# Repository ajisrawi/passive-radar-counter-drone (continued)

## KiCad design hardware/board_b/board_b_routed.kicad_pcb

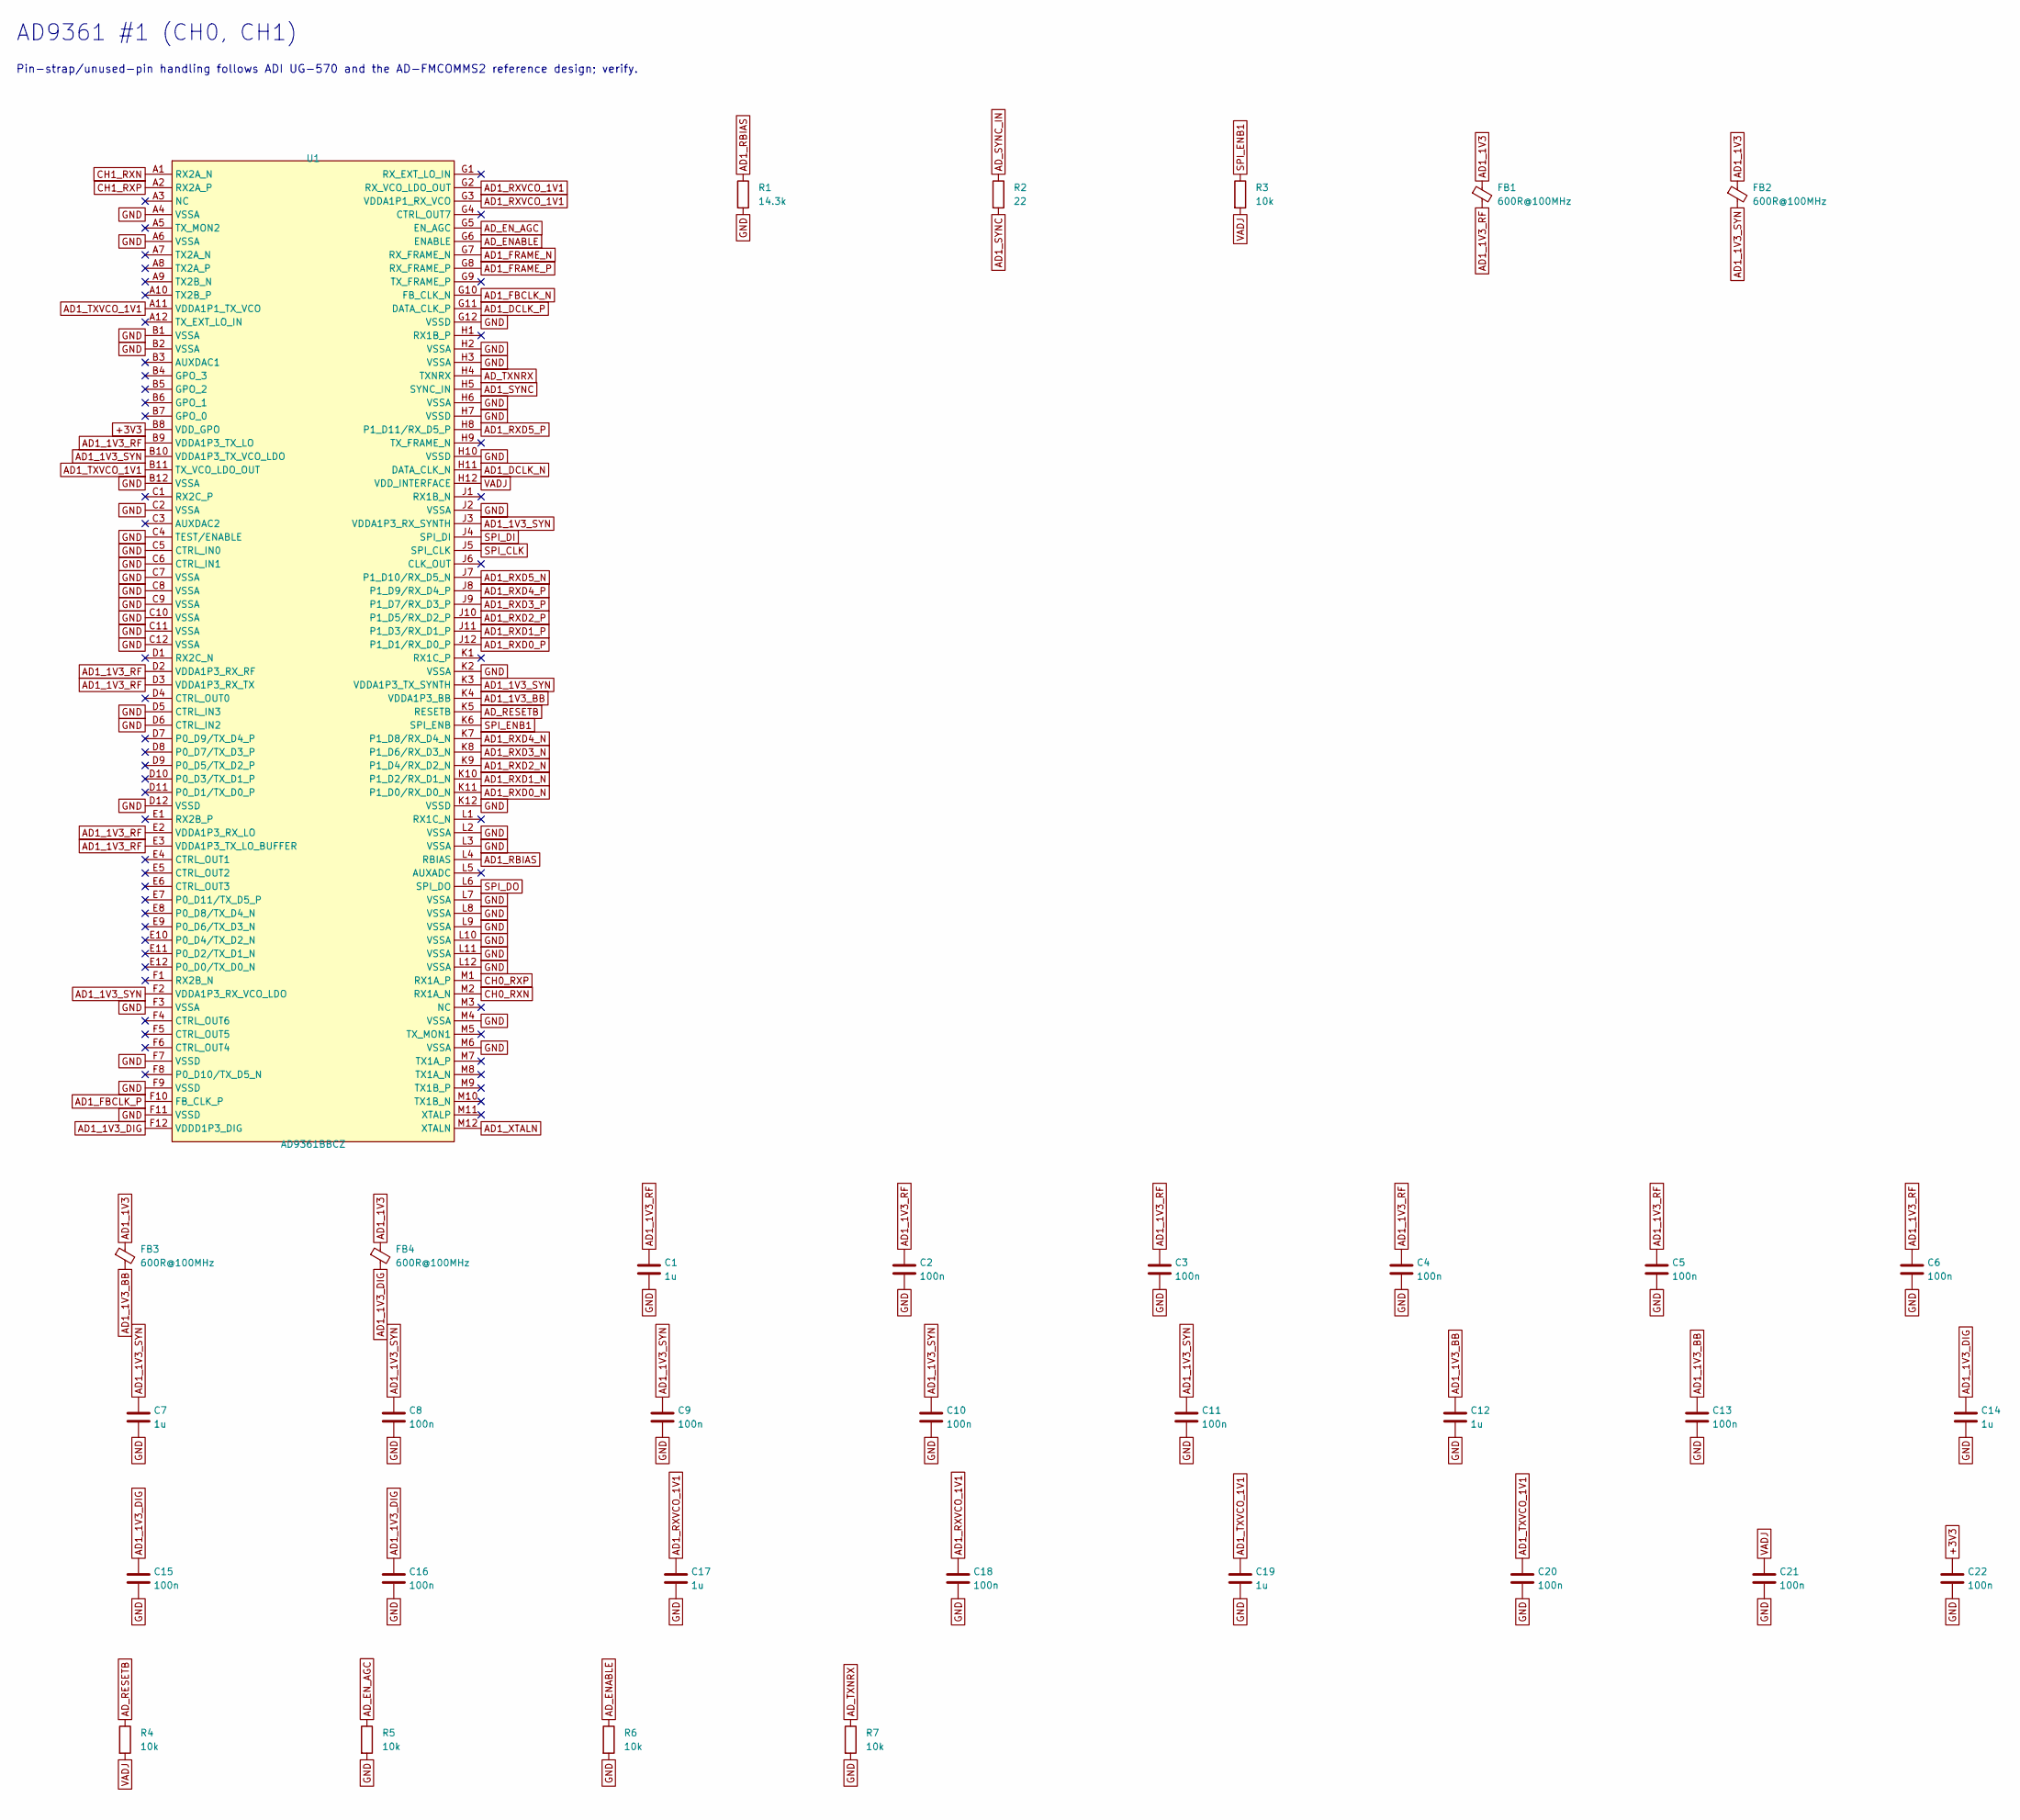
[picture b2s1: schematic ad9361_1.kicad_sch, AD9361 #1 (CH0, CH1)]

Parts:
C1, C7, C12, C14, C17, C19: 1u; C_0402_1005Metric; LCSC C52923
C2, C3, C4, C5, C6, C8, C9, C10, C11, C13, C15, C16, C18, C20, C21, C22: 100n; C_0402_1005Metric; LCSC C1525
FB1, FB2, FB3, FB4: 600R@100MHz; L_0603_1608Metric
R1: 14.3k; R_0402_1005Metric; Tolerance 1%
R2: 22; R_0402_1005Metric
R3, R4, R5, R6, R7: 10k; R_0402_1005Metric; LCSC C25744
U1: AD9361BBCZ; CSPBGA-144_L10.0-W10.0-R12-C12-P0.80-BL; MPN AD9361BBCZ; LCSC C515884

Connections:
+3V3: C22.1, U1.B8 (VDD_GPO); also elsewhere on the board
AD1_1V3: FB1.1, FB2.1, FB3.1, FB4.1; also elsewhere on the board
AD1_1V3_BB: C12.1, C13.1, FB3.2, U1.K4 (VDDA1P3_BB)
AD1_1V3_DIG: C14.1, C15.1, C16.1, FB4.2, U1.F12 (VDDD1P3_DIG)
AD1_1V3_RF: C1.1, C2.1, C3.1, C4.1, C5.1, C6.1, FB1.2, U1.B9 (VDDA1P3_TX_LO), U1.D2 (VDDA1P3_RX_RF), U1.D3 (VDDA1P3_RX_TX), U1.E2 (VDDA1P3_RX_LO), U1.E3 (VDDA1P3_TX_LO_BUFFER)
AD1_1V3_SYN: C7.1, C8.1, C9.1, C10.1, C11.1, FB2.2, U1.B10 (VDDA1P3_TX_VCO_LDO), U1.F2 (VDDA1P3_RX_VCO_LDO), U1.J3 (VDDA1P3_RX_SYNTH), U1.K3 (VDDA1P3_TX_SYNTH)
AD1_DCLK_N: U1.H11 (DATA_CLK_N); also elsewhere on the board
AD1_DCLK_P: U1.G11 (DATA_CLK_P); also elsewhere on the board
AD1_FBCLK_N: U1.G10 (FB_CLK_N); also elsewhere on the board
AD1_FBCLK_P: U1.F10 (FB_CLK_P); also elsewhere on the board
AD1_FRAME_N: U1.G7 (RX_FRAME_N); also elsewhere on the board
AD1_FRAME_P: U1.G8 (RX_FRAME_P); also elsewhere on the board
AD1_RBIAS: R1.1, U1.L4 (RBIAS)
AD1_RXD0_N: U1.K11 (P1_D0/RX_D0_N); also elsewhere on the board
AD1_RXD0_P: U1.J12 (P1_D1/RX_D0_P); also elsewhere on the board
AD1_RXD1_N: U1.K10 (P1_D2/RX_D1_N); also elsewhere on the board
AD1_RXD1_P: U1.J11 (P1_D3/RX_D1_P); also elsewhere on the board
AD1_RXD2_N: U1.K9 (P1_D4/RX_D2_N); also elsewhere on the board
AD1_RXD2_P: U1.J10 (P1_D5/RX_D2_P); also elsewhere on the board
AD1_RXD3_N: U1.K8 (P1_D6/RX_D3_N); also elsewhere on the board
AD1_RXD3_P: U1.J9 (P1_D7/RX_D3_P); also elsewhere on the board
AD1_RXD4_N: U1.K7 (P1_D8/RX_D4_N); also elsewhere on the board
AD1_RXD4_P: U1.J8 (P1_D9/RX_D4_P); also elsewhere on the board
AD1_RXD5_N: U1.J7 (P1_D10/RX_D5_N); also elsewhere on the board
AD1_RXD5_P: U1.H8 (P1_D11/RX_D5_P); also elsewhere on the board
AD1_RXVCO_1V1: C17.1, C18.1, U1.G2 (RX_VCO_LDO_OUT), U1.G3 (VDDA1P1_RX_VCO)
AD1_SYNC: R2.2, U1.H5 (SYNC_IN)
AD1_TXVCO_1V1: C19.1, C20.1, U1.A11 (VDDA1P1_TX_VCO), U1.B11 (TX_VCO_LDO_OUT)
AD1_XTALN: U1.M12 (XTALN); also elsewhere on the board
AD_ENABLE: R6.1, U1.G6 (ENABLE); also elsewhere on the board
AD_EN_AGC: R5.1, U1.G5 (EN_AGC); also elsewhere on the board
AD_RESETB: R4.1, U1.K5 (RESETB); also elsewhere on the board
AD_SYNC_IN: R2.1; also elsewhere on the board
AD_TXNRX: R7.1, U1.H4 (TXNRX); also elsewhere on the board
CH0_RXN: U1.M2 (RX1A_N); also elsewhere on the board
CH0_RXP: U1.M1 (RX1A_P); also elsewhere on the board
CH1_RXN: U1.A1 (RX2A_N); also elsewhere on the board
CH1_RXP: U1.A2 (RX2A_P); also elsewhere on the board
GND: C1.2, C2.2, C3.2, C4.2, C5.2, C6.2, C7.2, C8.2, C9.2, C10.2, C11.2, C12.2, C13.2, C14.2, C15.2, C16.2, C17.2, C18.2, C19.2, C20.2, C21.2, C22.2, R1.2, R5.2, R6.2, R7.2, U1.A4 (VSSA), U1.A6 (VSSA), U1.B1 (VSSA), U1.B2 (VSSA), U1.B12 (VSSA), U1.C2 (VSSA), U1.C4 (TEST/ENABLE), U1.C5 (CTRL_IN0), U1.C6 (CTRL_IN1), U1.C7 (VSSA), U1.C8 (VSSA), U1.C9 (VSSA), U1.C10 (VSSA), U1.C11 (VSSA), U1.C12 (VSSA), U1.D5 (CTRL_IN3), U1.D6 (CTRL_IN2), U1.D12 (VSSD), U1.F3 (VSSA), U1.F7 (VSSD), U1.F9 (VSSD), U1.F11 (VSSD), U1.G12 (VSSD), U1.H2 (VSSA), U1.H3 (VSSA), U1.H6 (VSSA), U1.H7 (VSSD), U1.H10 (VSSD), U1.J2 (VSSA), U1.K2 (VSSA), U1.K12 (VSSD), U1.L2 (VSSA), U1.L3 (VSSA), U1.L7 (VSSA), U1.L8 (VSSA), U1.L9 (VSSA), U1.L10 (VSSA), U1.L11 (VSSA), U1.L12 (VSSA), U1.M4 (VSSA), U1.M6 (VSSA); also elsewhere on the board
SPI_CLK: U1.J5 (SPI_CLK); also elsewhere on the board
SPI_DI: U1.J4 (SPI_DI); also elsewhere on the board
SPI_DO: U1.L6 (SPI_DO); also elsewhere on the board
SPI_ENB1: R3.1, U1.K6 (SPI_ENB); also elsewhere on the board
VADJ: C21.1, R3.2, R4.2, U1.H12 (VDD_INTERFACE); also elsewhere on the board

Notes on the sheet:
AD9361 #1 (CH0, CH1)
Pin-strap/unused-pin handling follows ADI UG-570 and the AD-FMCOMMS2 reference design; verify.

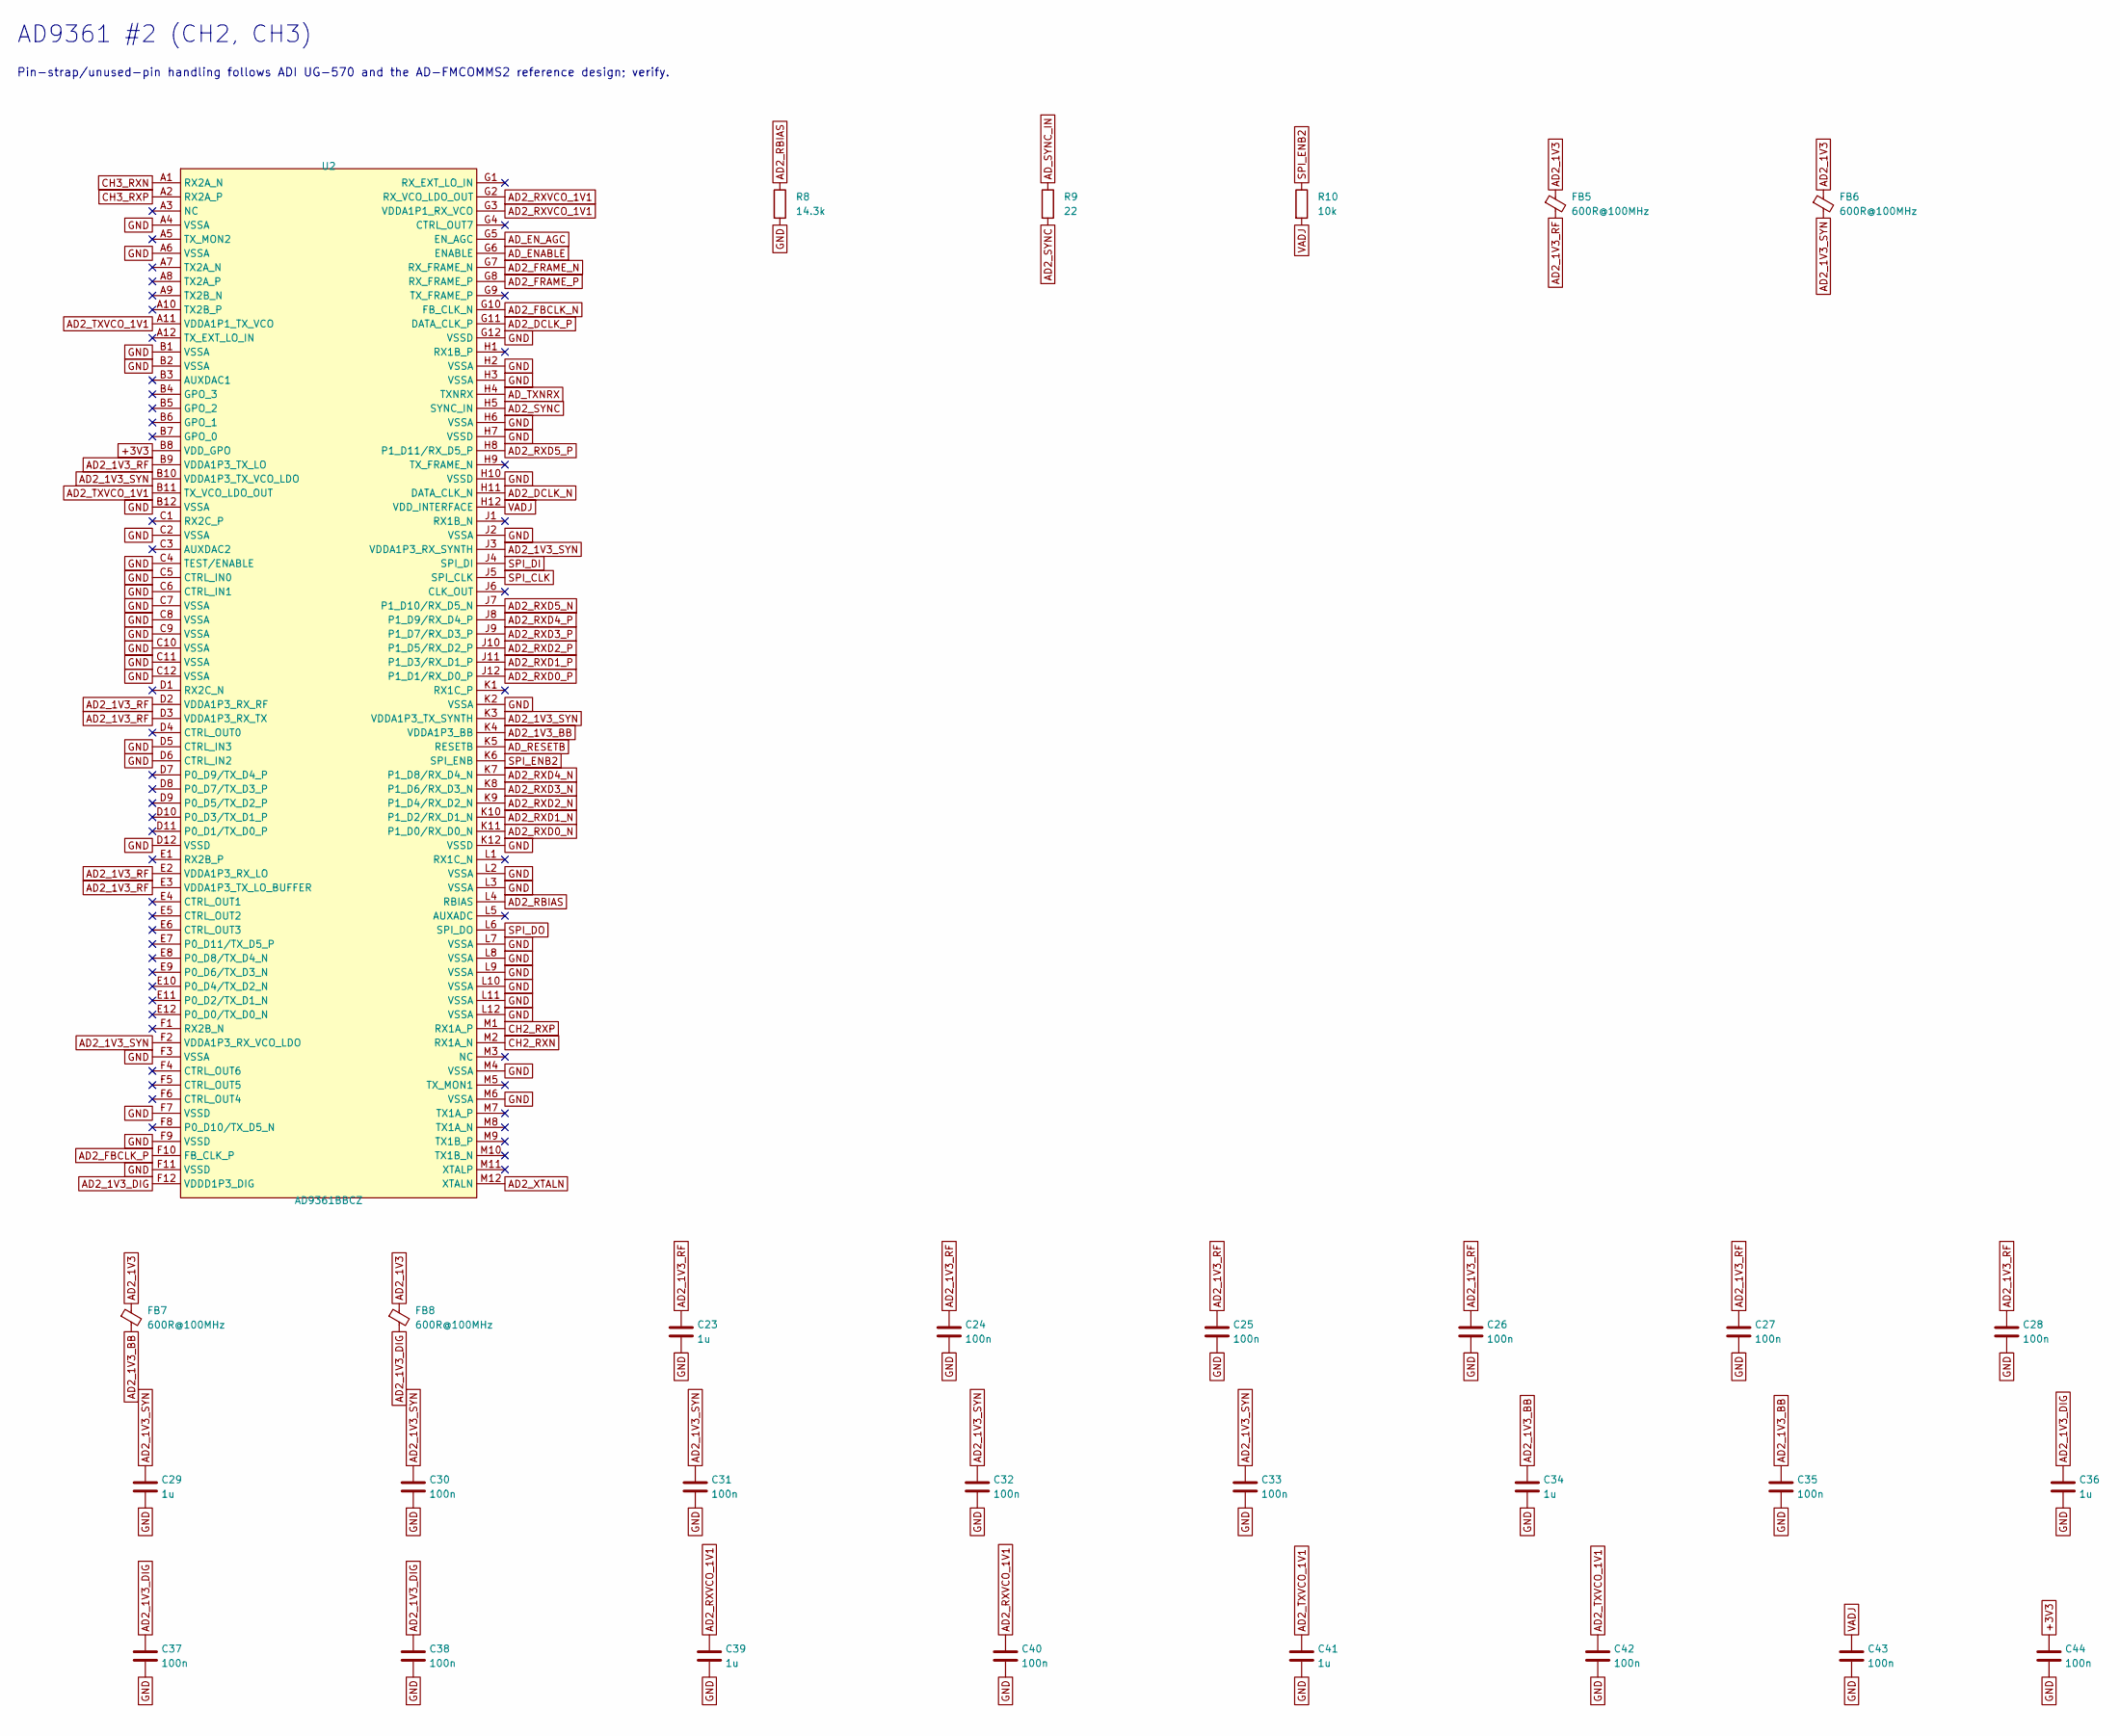
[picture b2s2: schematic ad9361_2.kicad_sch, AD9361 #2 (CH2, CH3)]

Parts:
C23, C29, C34, C36, C39, C41: 1u; C_0402_1005Metric; LCSC C52923
C24, C25, C26, C27, C28, C30, C31, C32, C33, C35, C37, C38, C40, C42, C43, C44: 100n; C_0402_1005Metric; LCSC C1525
FB5, FB6, FB7, FB8: 600R@100MHz; L_0603_1608Metric
R8: 14.3k; R_0402_1005Metric; Tolerance 1%
R9: 22; R_0402_1005Metric
R10: 10k; R_0402_1005Metric; LCSC C25744
U2: AD9361BBCZ; CSPBGA-144_L10.0-W10.0-R12-C12-P0.80-BL; MPN AD9361BBCZ; LCSC C515884

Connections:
+3V3: C44.1, U2.B8 (VDD_GPO); also elsewhere on the board
AD2_1V3: FB5.1, FB6.1, FB7.1, FB8.1; also elsewhere on the board
AD2_1V3_BB: C34.1, C35.1, FB7.2, U2.K4 (VDDA1P3_BB)
AD2_1V3_DIG: C36.1, C37.1, C38.1, FB8.2, U2.F12 (VDDD1P3_DIG)
AD2_1V3_RF: C23.1, C24.1, C25.1, C26.1, C27.1, C28.1, FB5.2, U2.B9 (VDDA1P3_TX_LO), U2.D2 (VDDA1P3_RX_RF), U2.D3 (VDDA1P3_RX_TX), U2.E2 (VDDA1P3_RX_LO), U2.E3 (VDDA1P3_TX_LO_BUFFER)
AD2_1V3_SYN: C29.1, C30.1, C31.1, C32.1, C33.1, FB6.2, U2.B10 (VDDA1P3_TX_VCO_LDO), U2.F2 (VDDA1P3_RX_VCO_LDO), U2.J3 (VDDA1P3_RX_SYNTH), U2.K3 (VDDA1P3_TX_SYNTH)
AD2_DCLK_N: U2.H11 (DATA_CLK_N); also elsewhere on the board
AD2_DCLK_P: U2.G11 (DATA_CLK_P); also elsewhere on the board
AD2_FBCLK_N: U2.G10 (FB_CLK_N); also elsewhere on the board
AD2_FBCLK_P: U2.F10 (FB_CLK_P); also elsewhere on the board
AD2_FRAME_N: U2.G7 (RX_FRAME_N); also elsewhere on the board
AD2_FRAME_P: U2.G8 (RX_FRAME_P); also elsewhere on the board
AD2_RBIAS: R8.1, U2.L4 (RBIAS)
AD2_RXD0_N: U2.K11 (P1_D0/RX_D0_N); also elsewhere on the board
AD2_RXD0_P: U2.J12 (P1_D1/RX_D0_P); also elsewhere on the board
AD2_RXD1_N: U2.K10 (P1_D2/RX_D1_N); also elsewhere on the board
AD2_RXD1_P: U2.J11 (P1_D3/RX_D1_P); also elsewhere on the board
AD2_RXD2_N: U2.K9 (P1_D4/RX_D2_N); also elsewhere on the board
AD2_RXD2_P: U2.J10 (P1_D5/RX_D2_P); also elsewhere on the board
AD2_RXD3_N: U2.K8 (P1_D6/RX_D3_N); also elsewhere on the board
AD2_RXD3_P: U2.J9 (P1_D7/RX_D3_P); also elsewhere on the board
AD2_RXD4_N: U2.K7 (P1_D8/RX_D4_N); also elsewhere on the board
AD2_RXD4_P: U2.J8 (P1_D9/RX_D4_P); also elsewhere on the board
AD2_RXD5_N: U2.J7 (P1_D10/RX_D5_N); also elsewhere on the board
AD2_RXD5_P: U2.H8 (P1_D11/RX_D5_P); also elsewhere on the board
AD2_RXVCO_1V1: C39.1, C40.1, U2.G2 (RX_VCO_LDO_OUT), U2.G3 (VDDA1P1_RX_VCO)
AD2_SYNC: R9.2, U2.H5 (SYNC_IN)
AD2_TXVCO_1V1: C41.1, C42.1, U2.A11 (VDDA1P1_TX_VCO), U2.B11 (TX_VCO_LDO_OUT)
AD2_XTALN: U2.M12 (XTALN); also elsewhere on the board
AD_ENABLE: U2.G6 (ENABLE); also elsewhere on the board
AD_EN_AGC: U2.G5 (EN_AGC); also elsewhere on the board
AD_RESETB: U2.K5 (RESETB); also elsewhere on the board
AD_SYNC_IN: R9.1; also elsewhere on the board
AD_TXNRX: U2.H4 (TXNRX); also elsewhere on the board
CH2_RXN: U2.M2 (RX1A_N); also elsewhere on the board
CH2_RXP: U2.M1 (RX1A_P); also elsewhere on the board
CH3_RXN: U2.A1 (RX2A_N); also elsewhere on the board
CH3_RXP: U2.A2 (RX2A_P); also elsewhere on the board
GND: C23.2, C24.2, C25.2, C26.2, C27.2, C28.2, C29.2, C30.2, C31.2, C32.2, C33.2, C34.2, C35.2, C36.2, C37.2, C38.2, C39.2, C40.2, C41.2, C42.2, C43.2, C44.2, R8.2, U2.A4 (VSSA), U2.A6 (VSSA), U2.B1 (VSSA), U2.B2 (VSSA), U2.B12 (VSSA), U2.C2 (VSSA), U2.C4 (TEST/ENABLE), U2.C5 (CTRL_IN0), U2.C6 (CTRL_IN1), U2.C7 (VSSA), U2.C8 (VSSA), U2.C9 (VSSA), U2.C10 (VSSA), U2.C11 (VSSA), U2.C12 (VSSA), U2.D5 (CTRL_IN3), U2.D6 (CTRL_IN2), U2.D12 (VSSD), U2.F3 (VSSA), U2.F7 (VSSD), U2.F9 (VSSD), U2.F11 (VSSD), U2.G12 (VSSD), U2.H2 (VSSA), U2.H3 (VSSA), U2.H6 (VSSA), U2.H7 (VSSD), U2.H10 (VSSD), U2.J2 (VSSA), U2.K2 (VSSA), U2.K12 (VSSD), U2.L2 (VSSA), U2.L3 (VSSA), U2.L7 (VSSA), U2.L8 (VSSA), U2.L9 (VSSA), U2.L10 (VSSA), U2.L11 (VSSA), U2.L12 (VSSA), U2.M4 (VSSA), U2.M6 (VSSA); also elsewhere on the board
SPI_CLK: U2.J5 (SPI_CLK); also elsewhere on the board
SPI_DI: U2.J4 (SPI_DI); also elsewhere on the board
SPI_DO: U2.L6 (SPI_DO); also elsewhere on the board
SPI_ENB2: R10.1, U2.K6 (SPI_ENB); also elsewhere on the board
VADJ: C43.1, R10.2, U2.H12 (VDD_INTERFACE); also elsewhere on the board

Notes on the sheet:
AD9361 #2 (CH2, CH3)
Pin-strap/unused-pin handling follows ADI UG-570 and the AD-FMCOMMS2 reference design; verify.

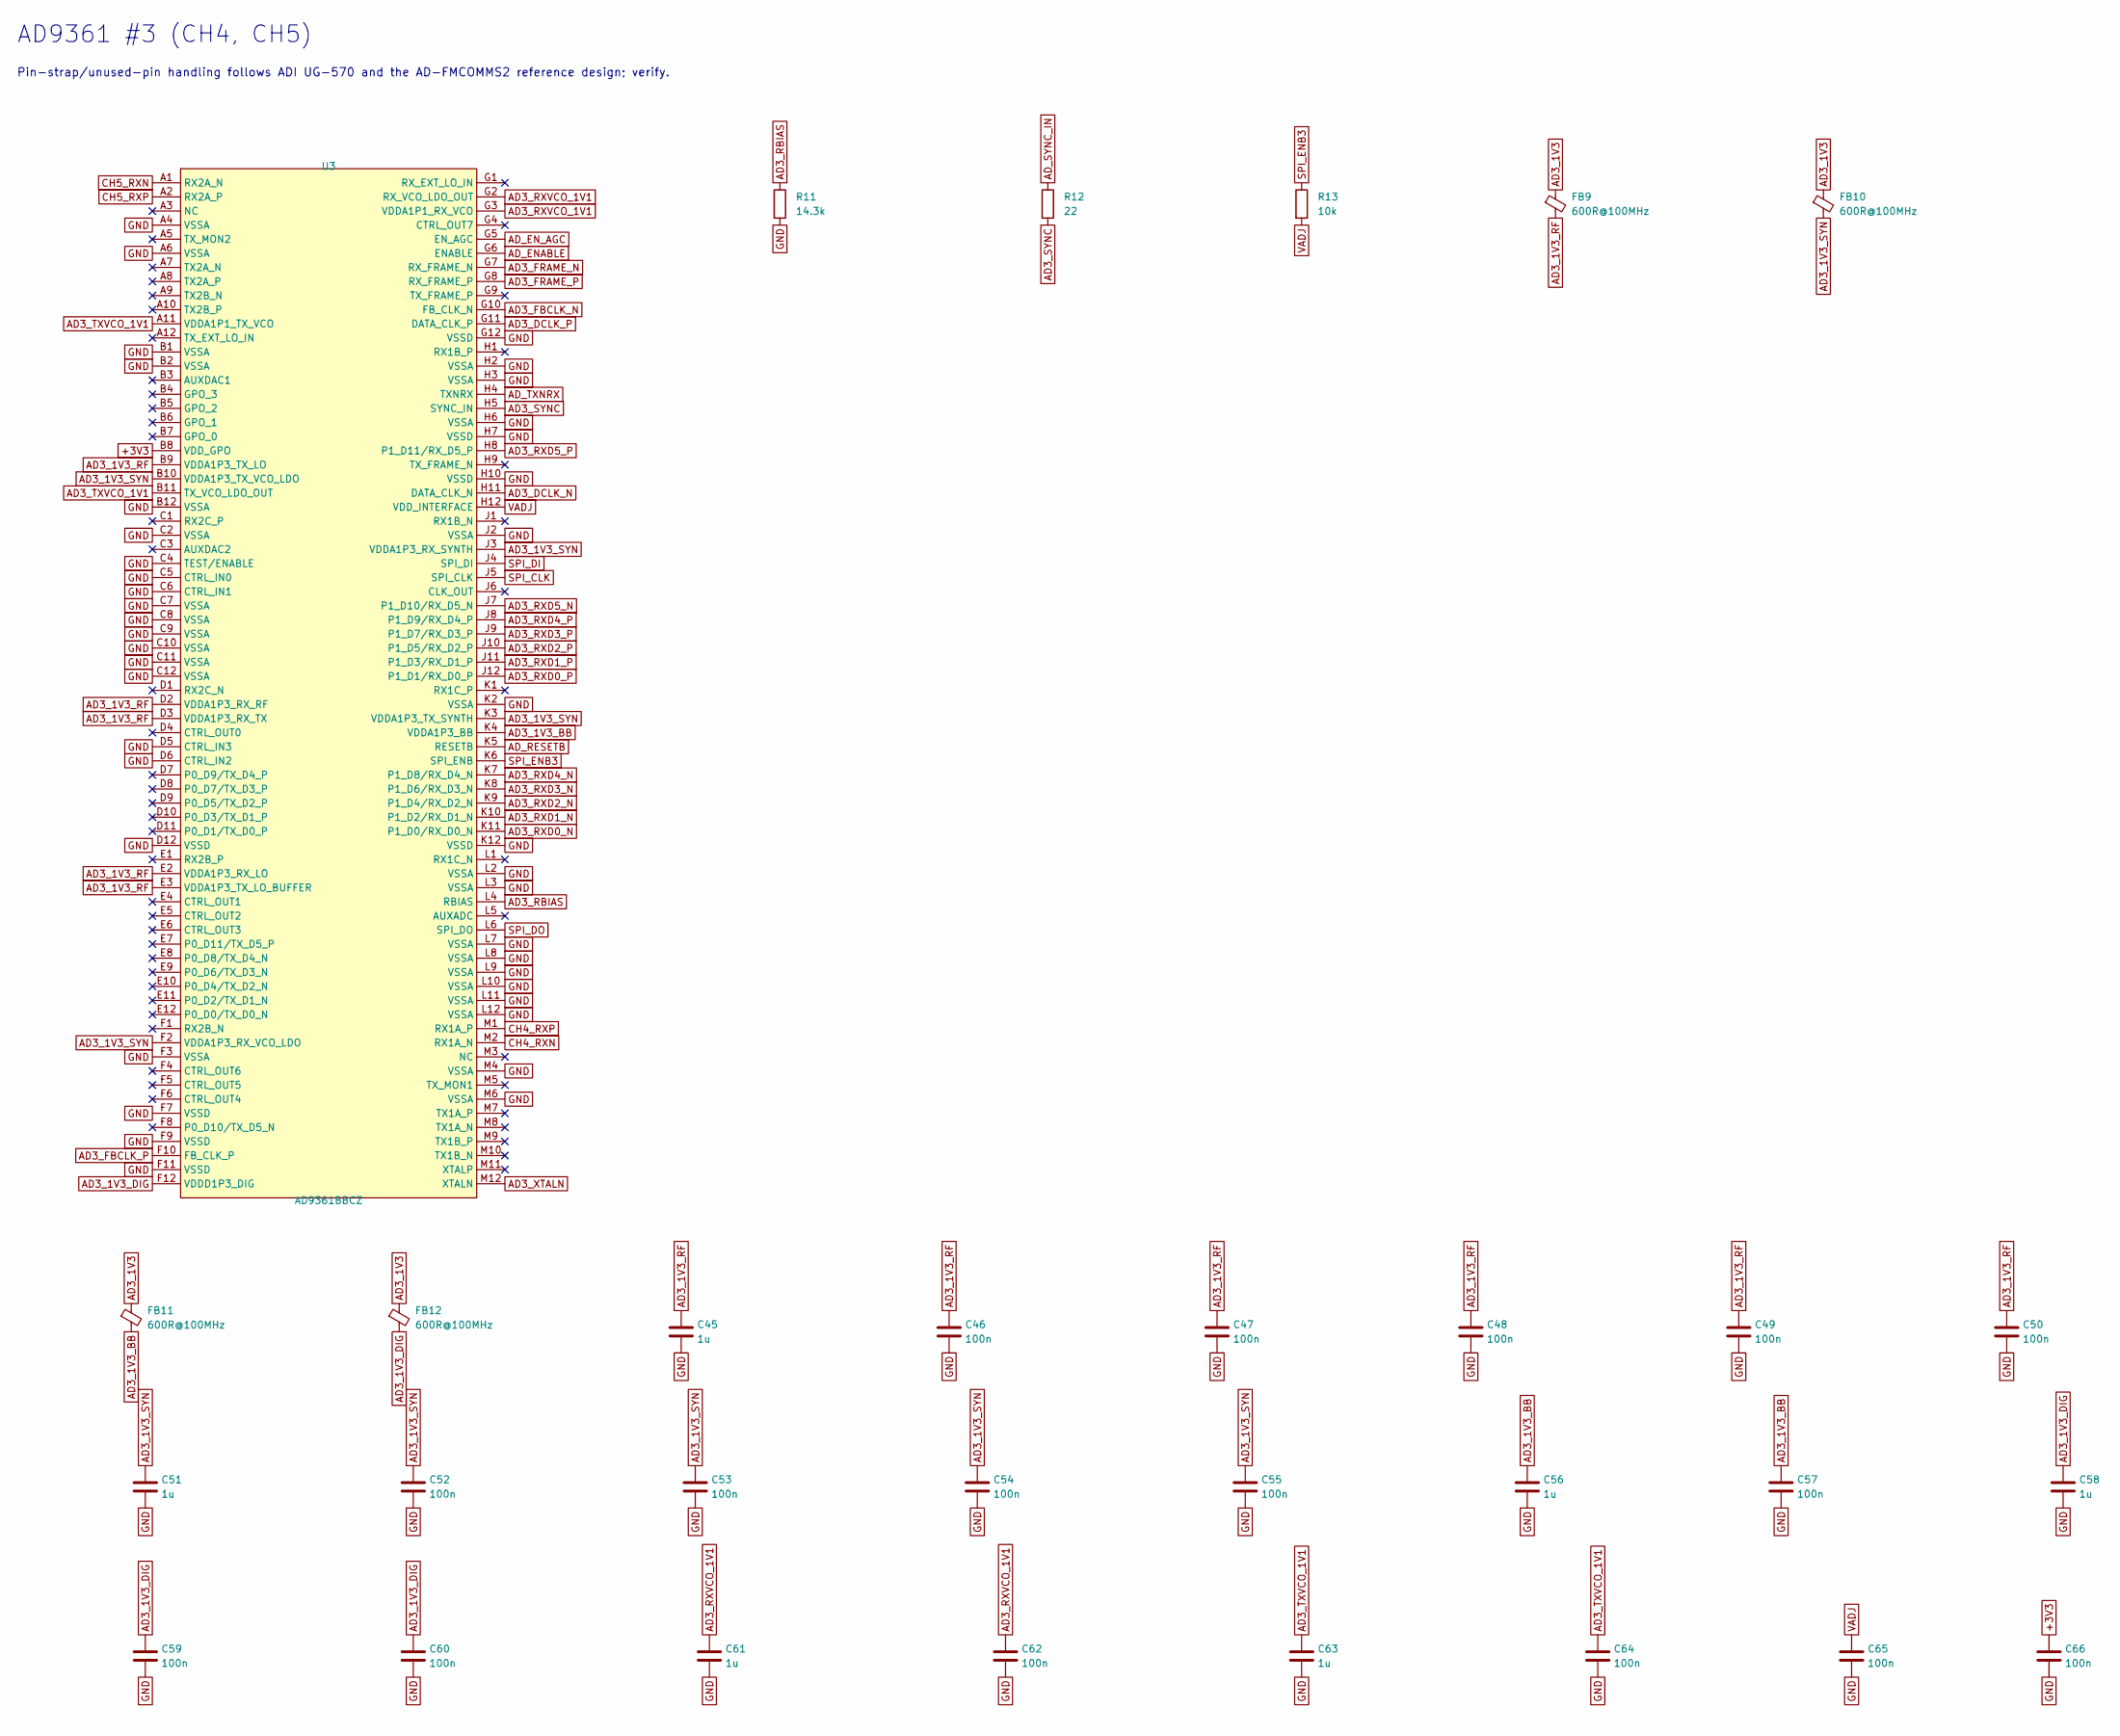
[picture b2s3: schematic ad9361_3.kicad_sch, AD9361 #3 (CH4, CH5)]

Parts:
C45, C51, C56, C58, C61, C63: 1u; C_0402_1005Metric; LCSC C52923
C46, C47, C48, C49, C50, C52, C53, C54, C55, C57, C59, C60, C62, C64, C65, C66: 100n; C_0402_1005Metric; LCSC C1525
FB9, FB10, FB11, FB12: 600R@100MHz; L_0603_1608Metric
R11: 14.3k; R_0402_1005Metric; Tolerance 1%
R12: 22; R_0402_1005Metric
R13: 10k; R_0402_1005Metric; LCSC C25744
U3: AD9361BBCZ; CSPBGA-144_L10.0-W10.0-R12-C12-P0.80-BL; MPN AD9361BBCZ; LCSC C515884

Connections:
+3V3: C66.1, U3.B8 (VDD_GPO); also elsewhere on the board
AD3_1V3: FB9.1, FB10.1, FB11.1, FB12.1; also elsewhere on the board
AD3_1V3_BB: C56.1, C57.1, FB11.2, U3.K4 (VDDA1P3_BB)
AD3_1V3_DIG: C58.1, C59.1, C60.1, FB12.2, U3.F12 (VDDD1P3_DIG)
AD3_1V3_RF: C45.1, C46.1, C47.1, C48.1, C49.1, C50.1, FB9.2, U3.B9 (VDDA1P3_TX_LO), U3.D2 (VDDA1P3_RX_RF), U3.D3 (VDDA1P3_RX_TX), U3.E2 (VDDA1P3_RX_LO), U3.E3 (VDDA1P3_TX_LO_BUFFER)
AD3_1V3_SYN: C51.1, C52.1, C53.1, C54.1, C55.1, FB10.2, U3.B10 (VDDA1P3_TX_VCO_LDO), U3.F2 (VDDA1P3_RX_VCO_LDO), U3.J3 (VDDA1P3_RX_SYNTH), U3.K3 (VDDA1P3_TX_SYNTH)
AD3_DCLK_N: U3.H11 (DATA_CLK_N); also elsewhere on the board
AD3_DCLK_P: U3.G11 (DATA_CLK_P); also elsewhere on the board
AD3_FBCLK_N: U3.G10 (FB_CLK_N); also elsewhere on the board
AD3_FBCLK_P: U3.F10 (FB_CLK_P); also elsewhere on the board
AD3_FRAME_N: U3.G7 (RX_FRAME_N); also elsewhere on the board
AD3_FRAME_P: U3.G8 (RX_FRAME_P); also elsewhere on the board
AD3_RBIAS: R11.1, U3.L4 (RBIAS)
AD3_RXD0_N: U3.K11 (P1_D0/RX_D0_N); also elsewhere on the board
AD3_RXD0_P: U3.J12 (P1_D1/RX_D0_P); also elsewhere on the board
AD3_RXD1_N: U3.K10 (P1_D2/RX_D1_N); also elsewhere on the board
AD3_RXD1_P: U3.J11 (P1_D3/RX_D1_P); also elsewhere on the board
AD3_RXD2_N: U3.K9 (P1_D4/RX_D2_N); also elsewhere on the board
AD3_RXD2_P: U3.J10 (P1_D5/RX_D2_P); also elsewhere on the board
AD3_RXD3_N: U3.K8 (P1_D6/RX_D3_N); also elsewhere on the board
AD3_RXD3_P: U3.J9 (P1_D7/RX_D3_P); also elsewhere on the board
AD3_RXD4_N: U3.K7 (P1_D8/RX_D4_N); also elsewhere on the board
AD3_RXD4_P: U3.J8 (P1_D9/RX_D4_P); also elsewhere on the board
AD3_RXD5_N: U3.J7 (P1_D10/RX_D5_N); also elsewhere on the board
AD3_RXD5_P: U3.H8 (P1_D11/RX_D5_P); also elsewhere on the board
AD3_RXVCO_1V1: C61.1, C62.1, U3.G2 (RX_VCO_LDO_OUT), U3.G3 (VDDA1P1_RX_VCO)
AD3_SYNC: R12.2, U3.H5 (SYNC_IN)
AD3_TXVCO_1V1: C63.1, C64.1, U3.A11 (VDDA1P1_TX_VCO), U3.B11 (TX_VCO_LDO_OUT)
AD3_XTALN: U3.M12 (XTALN); also elsewhere on the board
AD_ENABLE: U3.G6 (ENABLE); also elsewhere on the board
AD_EN_AGC: U3.G5 (EN_AGC); also elsewhere on the board
AD_RESETB: U3.K5 (RESETB); also elsewhere on the board
AD_SYNC_IN: R12.1; also elsewhere on the board
AD_TXNRX: U3.H4 (TXNRX); also elsewhere on the board
CH4_RXN: U3.M2 (RX1A_N); also elsewhere on the board
CH4_RXP: U3.M1 (RX1A_P); also elsewhere on the board
CH5_RXN: U3.A1 (RX2A_N); also elsewhere on the board
CH5_RXP: U3.A2 (RX2A_P); also elsewhere on the board
GND: C45.2, C46.2, C47.2, C48.2, C49.2, C50.2, C51.2, C52.2, C53.2, C54.2, C55.2, C56.2, C57.2, C58.2, C59.2, C60.2, C61.2, C62.2, C63.2, C64.2, C65.2, C66.2, R11.2, U3.A4 (VSSA), U3.A6 (VSSA), U3.B1 (VSSA), U3.B2 (VSSA), U3.B12 (VSSA), U3.C2 (VSSA), U3.C4 (TEST/ENABLE), U3.C5 (CTRL_IN0), U3.C6 (CTRL_IN1), U3.C7 (VSSA), U3.C8 (VSSA), U3.C9 (VSSA), U3.C10 (VSSA), U3.C11 (VSSA), U3.C12 (VSSA), U3.D5 (CTRL_IN3), U3.D6 (CTRL_IN2), U3.D12 (VSSD), U3.F3 (VSSA), U3.F7 (VSSD), U3.F9 (VSSD), U3.F11 (VSSD), U3.G12 (VSSD), U3.H2 (VSSA), U3.H3 (VSSA), U3.H6 (VSSA), U3.H7 (VSSD), U3.H10 (VSSD), U3.J2 (VSSA), U3.K2 (VSSA), U3.K12 (VSSD), U3.L2 (VSSA), U3.L3 (VSSA), U3.L7 (VSSA), U3.L8 (VSSA), U3.L9 (VSSA), U3.L10 (VSSA), U3.L11 (VSSA), U3.L12 (VSSA), U3.M4 (VSSA), U3.M6 (VSSA); also elsewhere on the board
SPI_CLK: U3.J5 (SPI_CLK); also elsewhere on the board
SPI_DI: U3.J4 (SPI_DI); also elsewhere on the board
SPI_DO: U3.L6 (SPI_DO); also elsewhere on the board
SPI_ENB3: R13.1, U3.K6 (SPI_ENB); also elsewhere on the board
VADJ: C65.1, R13.2, U3.H12 (VDD_INTERFACE); also elsewhere on the board

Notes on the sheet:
AD9361 #3 (CH4, CH5)
Pin-strap/unused-pin handling follows ADI UG-570 and the AD-FMCOMMS2 reference design; verify.
